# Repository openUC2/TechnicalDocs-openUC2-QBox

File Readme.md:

# Technical Documentation

1. **[Bill_of_Materials (BOM)](./Bill_of_Materials)**: Contains a detailed list of all parts and materials used in the project, including suppliers and part numbers.

2. **[Certifications](./Certifications)**: Holds all the relevant certification documents, such as CE compliance and other regulatory certifications your product meets.

3. **[Change_Logs](./Change_Logs)**: Records all changes made to the project over time, providing a historical record of modifications and updates.

4. **[Contributions](./Contributions)**: Guidelines and information for anyone who wants to contribute to the project, outlining how they can get involved.

5. **[Issue_Tracking](./Issue_Tracking)**: A space for tracking and managing issues, bugs, and potential improvements for the project.

6. **[Legal_and_Regulatory](./Legal_and_Regulatory)**: Contains legal documents, regulatory compliance statements, and warranty information.

7. **[Production_Files](./Production_Files)**: Includes all production-related files such as CAD designs, firmware, and software tools.

8. **[Quality_Control](./Quality_Control)**: Documentation on quality control measures, including inspection reports and testing procedures.

9. **[Readme.md](./Readme.md)**: The main document providing an overview of the project, its structure, and how to navigate the repository.

10. **[Risk_Assessment](./Risk_Assessment)**: Contains risk assessment reports, outlining potential risks and mitigation strategies.

11. **[Technical_Documents](./Technical_Documents)**: Holds technical documentation such as assembly guides, user manuals, and design specifications.

## Tasks

Die Hauptziele, Aufgabenpakete und Meilensteine des QuantumMiniLabs-Projekts, an dem openUC2 beteiligt ist, umfassen folgende zentrale Aspekte:

### Hauptziele
1. **Entwicklung von Open-Source-Experimentierkits** zur Wissensvermittlung der Quantentechnologien der zweiten Generation.
2. **Ausstattung von 100 Lernorten** mit dem Basis-Kit „Coherent Control“, das eine kosteneffiziente und skalierbare Plattform zur Verfügung stellt.
3. **Schaffung einer nachhaltigen Open-Source-Community**, die den Austausch und die Weiterentwicklung der Technologien unterstützt.
4. **Integration von Quantenphotonik** in modulare Baukastensysteme, um sie einer breiten Masse zugänglich zu machen.
5. **Rechtliche und technische Absicherung**, um eine nachhaltige Verwertung der Ergebnisse sicherzustellen.

### Hauptaufgabenpakete (AP)
1. **Entwicklung der Open-Innovation-Experimentalumgebung (AP1)**:
   - Forschung und Entwicklung des Basis-Kits „Coherent Control“ (AP1.2).
   - Entwicklung und Realisierung des Baukastensystems, das in 100 Lernorten eingesetzt werden soll (AP1.4).

2. **Outreach und Community-Building (AP2)**:
   - Aufbau einer QuantumMiniLabs-Gemeinschaft und Organisation von Veranstaltungen wie Hackathons und Workshops (AP2.1).
   - Testen der Kits an den Lernorten und kontinuierliche Verbesserung durch Feedback (AP2.2).

3. **Nachhaltigkeit und Geschäftsmodell (AP3)**:
   - Entwicklung eines Open-Source-Geschäftsmodells (AP3.2).
   - Rechtliche und technische Absicherung der Kits, einschließlich Zertifizierungsfragen und Haftung (AP3.1).
   - Planung der Produktion und Identifikation von Lieferanten für die Kleinserienproduktion (AP3.3).

### Notwendige Checkpunkte
1. **Prototypenentwicklung**: Erste Prototypen des Basis-Kits müssen produziert und mit Testgruppen evaluiert werden (innerhalb der ersten 18 Monate).
2. **Community-Building und Tests**: Es müssen mindestens 100 Lernorte mit den Kits ausgestattet und diese in praxisnahen Experimenten getestet werden.
3. **Nachhaltigkeitsstrategie**: Es muss ein nachhaltiges Geschäftsmodell entwickelt und die rechtliche Absicherung sichergestellt werden.
4. **Produktion und Distribution**: Die Kleinserienproduktion muss nach erfolgreichen Prototypentests geplant und umgesetzt werden.

Durch diese Struktur wird das Projekt auf technische Innovation, Community-Aufbau und wirtschaftliche Nachhaltigkeit ausgerichtet【4†source】.

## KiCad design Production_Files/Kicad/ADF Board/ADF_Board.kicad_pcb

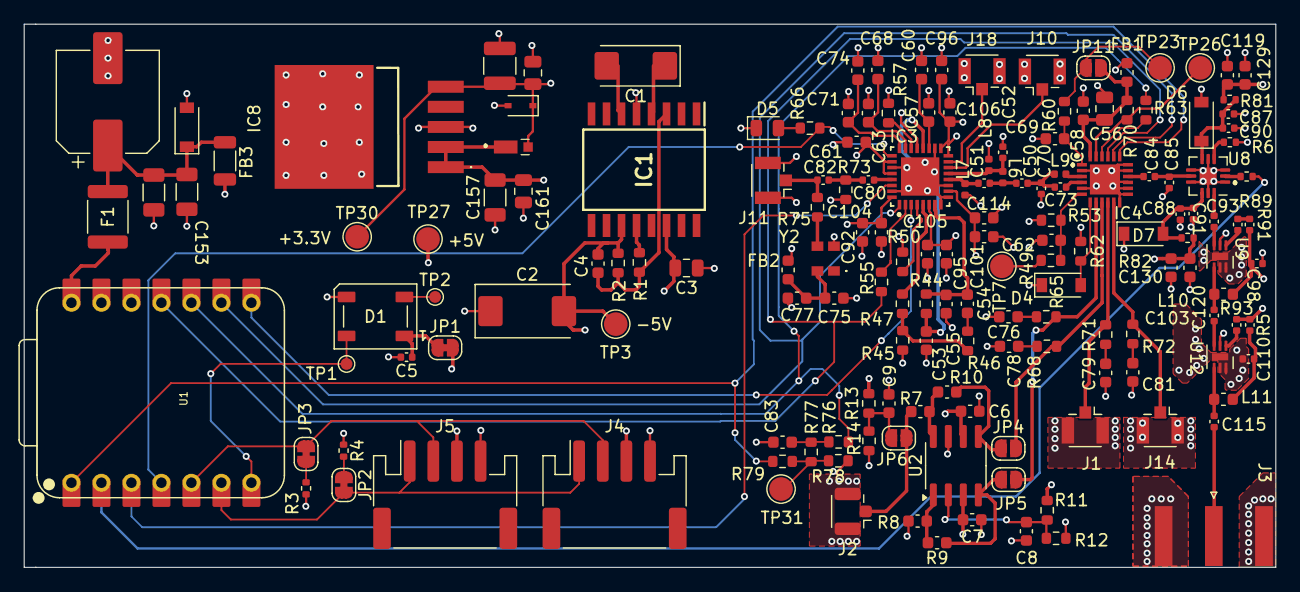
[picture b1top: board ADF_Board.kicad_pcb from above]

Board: 4 copper layers, 106.0 x 46.0 mm, 164 parts (0 on the bottom side), 91 nets.

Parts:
C1: 10u/Tantalum; CP_EIA-6032-15_Kemet-U
C2: 100u/Tantalum; CP_EIA-7343-20_Kemet-V
C3, C56: 4.7u; C_0805_2012Metric
C4: 2n; C_0603_1608Metric
C5: 100n/16V; C_0402_1005Metric
C6, C7, C60, C61, C68, C74, C75, C92, C95, C96, C101: 0.1u; C_0603_1608Metric
C8, C9: 10n; C_0603_1608Metric
C50: 10p; C_0402_1005Metric
C51, C52: 0.7p; C_0402_1005Metric
C53: 1.2n; C_0603_1608Metric
C54: 39n; C_0603_1608Metric
C55: 2.7n; C_0603_1608Metric
C57, C63, C71, C104, C105, C106, C114: 10p; C_0603_1608Metric
C58, C62: 1n; C_0603_1608Metric
C69, C76, C78, C79, C81, C119, C120: 100n; C_0603_1608Metric
C70, C85: 0.2p; C_0402_1005Metric
C73: 2p; C_0402_1005Metric
C77, C129, C130: 1u; C_0603_1608Metric
C80, C82: 1n; C_0402_1005Metric
C83: DNI; C_0603_1608Metric
C84, C93: 100p; C_0402_1005Metric
C87, C88: 1p; C_0402_1005Metric
C90, C91: 0.5p; C_0402_1005Metric
C98, C110: 0.1u; C_0402_1005Metric
C103, C115: 1000p; C_0402_1005Metric
C145: 470u; CP_Elec_8x10.5
C151: 220n; C_1206_3216Metric
C153: 100n; C_1206_3216Metric
C157: 1u; C_1206_3216Metric
C158, C161: 100n; C_0805_2012Metric
C162: 22u; C_1210_3225Metric
D1: WS2812B; LED_WS2812B_PLCC4_5.0x5.0mm_P3.2mm
D4: 1N4148; D_SOD-123
D5: LED; LED_0805_2012Metric
D6, D7: SZMMSZ5232BT1G; D_SOD-123
D12: DFLZ5V1Q-7; D_SOD-123
D15: https://www.mouser.de/datasheet/2/54/cdsod323_txx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; D_SOD-323
D19: PD3S220L-7; PD3S1407
F1: MINISMDC110F/24-2; Fuse_1812_4532Metric
FB1, FB2: MPZ1608S331AT; L_0603_1608Metric
FB3: Z1206C800APWST; L_1206_3216Metric
IC1: LT1054IDWG4; SOIC127P1030X265-16N
IC3: ADF4351BCPZ; QFN50P500X500X100-33N
IC4: LTC5589IUF#PBF; QFN50P400X400X80-25N-D
IC8: NCV4276CDS33R4G
J1, J2, J10, J11, J14, J18: Conn_Coaxial; U.FL_Hirose_U.FL-R-SMT-1_Vertical
J3: Conn_Coaxial; SMA_Amphenol_132289_EdgeMount
J4, J5: I2C_JST-PH_STEMMA; JST_PH_S4B-PH-SM4-TB_1x04-2iMP_P2.00mm_Horizontal
JP1: on-board-neopixel-power_NC; SolderJumper-2_P1.3mm_Bridged_RoundedPad1.0x1.5mm
JP2: I2C_SCL_pullup_NC; SolderJumper-2_P1.3mm_Bridged_RoundedPad1.0x1.5mm
JP3: I2C_SDA_pullup_NC; SolderJumper-2_P1.3mm_Bridged_RoundedPad1.0x1.5mm
JP4, JP5, JP6: SolderJumper_2_Open; SolderJumper-2_P1.3mm_Open_RoundedPad1.0x1.5mm
JP11: Jumper_2_Bridged; SolderJumper-2_P1.3mm_Open_RoundedPad1.0x1.5mm
L6, L7: 3.3n; L_0402_1005Metric
L8: 10n; L_0402_1005Metric
L9: 4.7n; L_0402_1005Metric
L10, L11: 47n; L_0603_1608Metric
R1: 20k; R_0603_1608Metric
R2: 102.6k; R_0603_1608Metric
R3, R4: 2k2; R_0402_1005Metric
R5, R91: 0R; C_0402_1005Metric
R6: 50; R_0402_1005Metric
R7, R8, R9, R10: 10k; C_0603_1608Metric
R11, R12: R; R_0603_1608Metric
R13: 1.15k; R_0603_1608Metric
R14: 500; R_0603_1608Metric
R44: 680R; R_0603_1608Metric
R45, R63, R75: 0R; R_0603_1608Metric
R46: 360R; R_0603_1608Metric
R47, R62, R76, R78, R79: DNI; R_0603_1608Metric
R49, R50, R70: 1k; R_0603_1608Metric
R53: 100k; R_0603_1608Metric
R55: 100R; R_0603_1608Metric
R57: 4.7k; R_0603_1608Metric
R60: 1R; R_0603_1608Metric
R65, R68, R71, R72: 49.9R; R_0603_1608Metric
R66: 750R; R_0603_1608Metric
R73: 49.9; R_0603_1608Metric
R77: 10R; R_0603_1608Metric
R80: 100R; R_0402_1005Metric
R81, R82: 11.5R; R_0402_1005Metric
R89, R93: 250R; C_0402_1005Metric
TP1: neopixel; TestPoint_Pad_D1.0mm
TP2: neopixel-extend; TestPoint_Pad_D1.0mm
TP3, TP27, TP30: TestPoint; TestPoint_Pad_D2.0mm
TP7: IQ_TTCK; TestPoint_Pad_D2.0mm
TP23: IQ_Vctrl; TestPoint_Pad_D2.0mm
TP26: IQ_EN; TestPoint_Pad_D2.0mm
TP31: IQ_SDO2; TestPoint_Pad_D2.0mm
U1: xiao_esp32s3; XIAO-ESP32S3-DIP
U2: AD8137; SOIC-8_3.9x4.9mm_P1.27mm
U8: M3SWA2-63DRC; QFN-12-1EP_3x3mm_P0.51mm_EP1.45x1.45mm
U9, U12: GRF2012; DFN-6-1EP_2x2mm_P0.5mm_EP0.6x1.37mm
Y2: TG2520SMN_30.000M-MCGNNM0; TG2520SMN30000MMCGNNM0

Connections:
+3.3V: C61.1, C92.1, C95.1, C96.1, C101.1, C104.1, C105.1, C106.1, C114.1, C158.1, C162.1, D15.1 (K), D19.2 (A), FB1.1, FB2.2, IC3.6 (VP), IC3.10 (AVDD), IC3.16 (VVCO_2), IC3.17 (VVCO), IC3.26 (PDBRF), IC3.28 (DVDD), IC3.32 (SDVDD), IC8.5 (Q), L7.1, L8.1, R3.1, R4.1, R50.1, R62.1, R78.2, TP30.1
+5V: C3.2, C7.2, C98.1, C119.1, C129.1, C157.2, C161.2, D19.1 (K), FB3.2, IC1.14 (VCC), IC8.1 (I), IC8.2 (INH), J4.3, J5.3, JP1.2 (B), L10.1, R5.1, R11.1, R13.2, R81.1, R91.2, R93.2, TP27.1, U2.3 (V+)
-5V: C2.2, C4.1, C6.1, C120.1, C130.1, IC1.11 (VOUT), R2.1, R82.1, TP3.1, U2.6 (V-)
/ESP Module/PLL_LD: IC3.25 (LD), R66.1, U1.4 (PA11_A3_D3)
/ESP Module/PLL_MuxOut: IC3.30 (MUXOUT), U1.3 (PA10_A2_D2)
/ESP Module/Switch1_TTL: R80.1, U1.2 (PA4_A1_D1)
/MW_Source/BBMI: IC4.9 (BBMI), JP4.2 (B), R68.1
/MW_Source/BBMQ: IC4.11 (BBMQ), J14.1 (In), R72.1
/MW_Source/BBPI: IC4.8 (BBPI), JP5.2 (B), R65.1
/MW_Source/BBPQ: IC4.10 (BBPQ), J1.1 (In), R71.1
/MW_Source/IQ_CSB: IC4.19 (CSB), R79.1, U1.1 (PA02_A0_D0)
/MW_Source/IQ_Out: C84.2, C85.1, U8.8 (RF-IN)
/MW_Source/IQ_SCLK: IC3.1 (CLK), IC4.20 (SCLK), U1.9 (PA7_A8_D8_SCK)
/MW_Source/IQ_SDI: IC4.21 (SDI), R55.1, U1.11 (PA6_A10_D10_MOSI)
/MW_Source/IQ_SDO: R63.2, R76.1, U1.10 (PA5_A9_D9_MISO)
/MW_Source/PLL_LE: IC3.3 (LE), U1.8 (PB09_D7_RX)
/MW_Source/PLL_Out: C50.1, C70.2, C73.1, L9.1
/MW_Source/PLL_VTune: C53.1, IC3.20 (VTUNE), R44.1
/MW_Source/RFB+: IC3.14 (RFOUTB+), J10.1 (In)
/MW_Source/RFB-: IC3.15 (RFOUTB-), J18.1 (In)
/MW_Source/RF_High_Out: C115.2, J3.1 (In)
/MW_Source/Switch1_Out: C93.2, U9.3 (IN)
GND: C2.1, C3.1, C5.2, C6.2, C7.1, C8.2, C9.2, C52.2, C53.2, C55.2, C56.2, C57.2, C58.2, C60.2, C61.2, C62.1, C63.2, C68.2, C69.2, C70.1, C71.2, C74.2, C75.2, C76.2, C77.2, C78.2, C79.2, C81.2, C83.2, C85.2, C87.1, C88.2, C90.1, C91.2, C92.2, C95.2, C96.2, C98.2, C101.2, C104.2, C105.2, C106.2, C110.2, C114.2, C119.2, C120.2, C129.2, C130.2, C145.2, C151.2, C153.2, C157.1, C158.2, C161.1, C162.2, D1.3 (VSS), D4.1 (K), D5.1 (K), D6.2 (A), D7.1 (K), D12.2 (A), D15.2 (A), IC1.5 (GND), IC3.8 (CPGND), IC3.9 (AGND), IC3.11 (AGNDVCO_2), IC3.18 (AGNDVCO_3), IC3.21 (AGNDVCO), IC3.27 (DGND), IC3.31 (SDGND), IC3.33 (EP), IC4.2 (GND_1), IC4.5 (GND_2), IC4.12 (GND_3), IC4.13 (GND_4), IC4.14 (GND_5), IC4.15 (GND_6), IC4.17 (GND_7), IC4.18 (GND_8), IC4.25 (GND_9), IC8.3 (GND_1), IC8.6 (GND_2), J1.2 (Ext), J2.2 (Ext), J3.2 (Ext), J4.4, J5.4, J10.2 (Ext), J11.2 (Ext), J14.2 (Ext), J18.2 (Ext), R6.1, R8.1, R12.2, R14.1, R45.1, R53.1, R57.2, R73.2, U1.13 (GND), U2.7 (~SHDN), U8.1 (GND), U8.3 (TTL_GND), U8.5 (GND), U8.7 (GND), U8.9 (GND), U8.11 (GND), U8.13 (PAD), U9.2 (GND), U9.5 (GND), U9.6 (GND), U9.7 (EP), U12.2 (GND), U12.5 (GND), U12.6 (GND), U12.7 (EP), Y2.2 (GND)
I2C_SCL: J4.1, J5.1, JP2.2 (B), U1.6 (PA9_A5_D5_SCL)
I2C_SDA: J4.2, J5.2, JP3.2 (B), U1.5 (PA8_A4_D4_SDA)
unnamed: C50.2, C51.2, L6.1
unnamed: C54.2, R46.2
unnamed: C76.1, R65.2
unnamed: C78.1, R68.2
unnamed: C79.1, R71.2
unnamed: C80.2, C82.1, R73.1
unnamed: C81.1, R72.2
unnamed: C83.1, R76.2, R77.1
unnamed: C103.1, L10.2, U9.4
unnamed: C110.1, L11.1, R5.2
unnamed: C115.1, L11.2, U12.4
unnamed: D1.2 (DOUT), TP2.1
unnamed: C5.1, D1.1 (VDD), JP1.1 (A)
unnamed: D4.2 (A), IC4.7 (TEMP), R62.2
unnamed: D5.2 (A), R66.2
unnamed: C87.2, C90.2, D6.1 (K), R81.2, U8.6 (VDD)
unnamed: C88.1, C91.1, D7.2 (A), R82.2, U8.10 (VEE)
unnamed: C145.1, C151.1, C153.1, D12.1 (K), F1.2, FB3.1
unnamed: C1.1, IC1.4 (CAP+)
unnamed: C1.2, IC1.6 (CAP-)
unnamed: C4.2, IC1.3 (FB/SD), R1.2, R2.2
unnamed: IC1.12 (VREF), R1.1
unnamed: IC3.4 (CE), R50.2
unnamed: C54.1, C55.1, IC3.7 (CPOUT), R44.2
unnamed: IC3.2 (DATA), R55.2
unnamed: C80.1, IC3.29 (REFIN)
unnamed: C51.1, IC3.12 (RFOUTA+), L7.2
unnamed: C52.1, IC3.13 (RFOUTA-), L6.2, L8.2
unnamed: IC3.22 (RSET), R57.1
unnamed: IC3.5 (SW), R47.2
unnamed: C57.1, C60.1, IC3.19 (TEMP)
unnamed: C63.1, C68.1, IC3.23 (VCOM)
unnamed: C71.1, C74.1, IC3.24 (VREF)
unnamed: IC4.23 (EN), R70.2, TP26.1
unnamed: C73.2, IC4.4 (LOC)
unnamed: IC4.3 (LOL), L9.2
unnamed: C84.1, IC4.16 (RF)
unnamed: IC4.22 (SDO), R63.1
unnamed: C62.2, IC4.6 (TTCK), R49.2, R53.2
unnamed: C56.1, C58.1, FB1.2, IC4.24 (VCC), JP11.2 (B), R70.1
unnamed: C69.1, IC4.1 (VCTRL), R60.2
unnamed: J2.1 (In), JP6.1 (A), R7.1
unnamed: C82.2, J11.1 (In), R75.2
unnamed: JP2.1 (A), R4.2
unnamed: JP3.1 (A), R3.2
unnamed: JP4.1 (A), R10.2, U2.5 (-)
unnamed: JP5.1 (A), R9.2, U2.4 (+)
unnamed: C9.1, JP6.2 (B), R13.1, R14.2
unnamed: JP11.1 (A), R60.1, TP23.1
unnamed: R8.2, R9.1, U2.1 (-)
unnamed: R7.2, R10.1, U2.8 (+)
unnamed: R45.2, R46.1, R47.1
unnamed: R49.1, TP7.1
unnamed: R77.2, R78.1, R79.2, TP31.1
unnamed: R89.2, R91.1
unnamed: C8.1, R11.2, R12.1, U2.2 (VOCM)
unnamed: C93.1, U8.12 (RF-OUT1)
unnamed: R6.2, U8.4 (RF-OUT2)
unnamed: R80.2, U8.2 (TTL_IN)
unnamed: R89.1, U9.1 (EN)
unnamed: R93.1, U12.1 (EN)
unnamed: C103.2, U12.3 (IN)
unnamed: R75.1, Y2.3 (OUT)
unnamed: C75.1, C77.1, FB2.1, Y2.4 (VCC)
VDD: F1.1, U1.14 (5V)
neopixel: D1.4 (DIN), TP1.1, U1.7 (PB08_A6_TX)

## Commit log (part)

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2024-09-11 adding stps
2024-10-02 Adding additional resources from Nils regarding ODMR setup
2024-10-08 Adding CAD Files
2024-10-23 updating qbox certain parts
2024-10-29 updating printing files
2024-11-14 cleanup and update parts
2024-11-14 removing stls and updating ipts
2025-02-28 Desing Files für ODMR Platine
2025-03-14 adding xiao test report
2025-03-21 adjusting pinout based on pcb layout and integrate functionalities
2025-03-24 adding webpage
2025-03-26 adding canans files
2025-04-01 fixing canans code so that it works
2025-04-03 Update Firmware (Mix of Canan and Nils Work)
2025-04-04 adding obj
2025-04-09 updating firmware
2025-05-18 organizing files, adding new printing files based on V4
2025-05-20 Update adf4351.cpp
    Update on the third register to match the new oscillator.
2025-05-22 Fixing Arduino code so that at least this works stabily on esp32c3
2025-05-24 FW Works in Pio - single Wavelength
2025-05-25 new way of computing register values
2025-05-25 adding docs
2025-05-25 stop in case it's not needed
2025-05-29 Enabled pio build to include the local ADF4351 lib (and not fail like before)
2025-05-31 minor updates and data folder renaming
2025-05-31 renaming
2025-06-04 adding webserial
2025-06-05 moving towards headerfiles for website
2025-06-05 reverting homepage files
2025-06-05 Initial plan for issue
2025-06-05 Convert website files to header files - main implementation
2025-06-05 Remove large PNG file and cleanup temporary files
2025-06-05 Update GitHub Actions workflow to remove SPIFFS filesystem build and merge steps
2025-06-06 formatting
2025-09-15 cleaning up
2025-09-15 adding website files
2025-09-15 Initial plan
2025-09-15 Implement core ODMR firmware improvements: LED status, frequency fix, intensity monitoring, build system
2025-09-15 Complete remaining ODMR improvements: serial error handling, SPI optimization, WebSerial restrictions, frequency range fixes
2025-09-15 Add comprehensive implementation summary and finalize ODMR firmware improvements
2025-09-16 improve interaction with frontend-backend
2025-09-16 fixing cdn
2025-10-15 Initial exploration of ODMR Server website issue
2025-10-15 Fix static website routing and add image support
    - Add explicit root "/" handler to prevent redirection to /static/
    - Create image optimization script (optimize_image.py)
    - Create image-to-header converter (convert_image.py)
    - Optimize NVGitter.png from 515KB to 118KB (77% reduction)
    - Convert optimized image to header file format
    - Update main.cpp to serve image from PROGMEM
2025-10-15 Add website fix summary documentation
2025-10-15 Add comprehensive testing guide for website fixes
2025-10-16 Add serial status indicator and improve responsive layout
    - Add real-time serial message display with timestamps
    - Color-code messages (green for DATA, red for ERROR, blue for OK)
    - Auto-scroll to show newest messages
    - Keep only last 50 messages for memory efficiency
    - Improve responsive layout with better breakpoints
    - Increase right panel width from 300px to 350px on large screens
2025-10-19 fixing minor issues
2025-10-19 Reduce image size and add version information system
    Image Optimization:
    - Reduce image size from 600px to 300px (91.6% reduction)
    - New optimized image: 43KB (down from 118KB)
    - Header file: 261KB (down from 707KB)
    - ESP32C3 compatible - fixes boot loop issue
    Version Information System:
2025-10-20 Add multi-language support (German/English) to all pages
    Language Switcher:
    - Add language dropdown to navigation bar on all pages
    - Support German (Deutsch) and English languages
    - Persistent language selection via localStorage
    - Instant content update without page reload
    Translation Coverage:
2025-11-10 updating website
2025-11-24 Add ODMR_CAMERA firmware and improve captive portal
    Added new ODMR_CAMERA firmware project with camera control, serial protocol, and example Python display script. Improved captive portal detection in ODMR_Server by using HTTP 302 redirects for Androi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
2025-12-10 adding instant b-field measurement
2025-12-11 wip: direct magnetic field measurements
2026-01-15 Add GitHub Actions workflow to build ODMR firmware
    This workflow builds the ODMR firmware from an external repository and uploads the binaries for integration with the web flasher.
2026-01-22 bumping website
2026-02-16 Use SPIFFS partition for NV-Center image instead of header file
2026-02-16 Add comprehensive documentation for SPIFFS image solution
2026-02-16 Add comprehensive testing guide for SPIFFS image solution
2026-02-16 Add solution summary documenting SPIFFS approach for NV-Center image
2026-02-18 commeted out everything to fix #75, but couldnt test it
2026-02-18 removed Laserdiode einschalten button and its functions
2026-02-18 added back status led
2026-02-18 removed all laser related funktions and variables
2026-03-04 Improve ODMR_Server stability and web handling
    Add ISSUES.md and multiple server improvements to reduce client stalls and captive-portal churn: stop redirecting OS probe endpoints (return success codes), return 404 for unknown non-HTML assets and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
2026-03-04 Add ODMR web assets and SPIFFS CI build
    Add static web assets for ODMR_Server (HTML/CSS/JS/image files) and update the project to include them. Update CI workflow to trigger on Production_Files/Software/ODMR_Server/** and the new branch 'f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
2026-03-05 Add ESP32-C3 merge script and merged bin
    Add a PlatformIO extra script (scripts/merge_espwebtools.py) that merges bootloader, partitions, app and SPIFFS into a single firmware image and provides custom targets mergedbin and upload_merged fo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
2026-03-06 ODMR Server: docs, i18n, captive portal & fixes
    Expanded README with detailed build/flash/development guide, merged-binary workflow, esptool and web-flasher instructions, partition layout and troubleshooting. Updated prebuilt firmware image (build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
    Frontend changes: added null-guards when registering event listeners in messung.html to avoid errors if elements are missing; added data-lang-key attributes and an i18n script to ratio.html (DE/EN tr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
    Firmware changes: updated captive-portal endpoints in src/main.cpp to serve a sm
2026-03-09 Add SSE sweep streaming, client & portal fixes
    Implement Server-Sent-Events sweeping: add /sweep endpoint that streams frequency/intensity points (with averaging, settle time, point limit) and stops when the client disconnects. Update JS UI (mess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
2026-03-09 Embed website, add LED breathing, tweak thresholds
    Embed generated website assets into firmware and prefer PROGMEM pages over SPIFFS; add helpers to serve PROGMEM strings and update root handler. Implement LED breathing brightness (sinusoidal pulse) 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
2026-03-11 removed double bullet points in benötigte Komponenten
2026-03-12 Add sweep buffer and recovery endpoints
    Implement sweep recovery and stop controls: add a SweepDataPoint buffer (MAX_SWEEP_BUFFER) to store recent sweep points, track sweepInProgress and sweepStopRequested, and persist points during a swee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
    Other updates: bump build metadata (date/time/git hash), update README esptool path, add an image width attribute in index.html, reorder a serial unknown-command log
2026-03-13 Partner Logos added to info site
2026-03-13 Add why ODMR is cool text
2026-03-18 Added Partner Logos
2026-04-17 Add Scale Option Stretch
2026-05-21 Update ODMR server website and add flowchart
    Add flowchart assets (IMAGES/flowchart_xiao_odmr.svg and accompanying .pptx) and update server web content. Several website source headers and generated HTML pages under Production_Files/Software/ODM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
2026-05-21 update website
2026-06-01 Added a lookup table for maximal Intensity Values, depending on gain and integration time & Adjust Optimal Values
2026-06-01 Added Satuated Status to Justage Bar
2026-06-10 updating
2026-06-10 print build time/date
2026-06-10 legacy support
2026-06-10 fix legacy
2026-06-10 reorganising
2026-06-12 Certification for some components
    optics
    kinematic mirror mount
    JST cable
    USB cable
    Antenna cable
    tape pad
2026-06-12 Material of thermoplastic screw
2026-06-15 ESP32 C3 CE
2026-06-16 Certification 304 screws
2026-06-16 Add magnet information to readme
2026-06-17 Add info for galvanized screws and ABS screen
2026-06-25 adafruit CE
2026-06-25 Update readme with emission filter details
    Added information about emission filter and its source.
2026-06-29 ensure offset for c3 matches
2026-06-30 updating webserial website
